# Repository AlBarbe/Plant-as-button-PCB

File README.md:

<!-- HEADER -->
# Plant as Button — PCB 🌱🔌

Wouldn't be cool to use as a plant a touch sensor? Now it has a proper board to live on.
This repo hosts the hardware side of the project — the companion firmware (the code that actually reads the plant's touch) lives in [Plant-as-button](https://github.com/AlBarbe/Plant-as-button).

<!-- TABLE OF CONTENTS -->
<!--
<details>
  <summary>Table of contenent</summary>
    <ul>
      <li></li><a href="#introduction">Introduction</a></li>
      <li></li><a href="#how-it-works">How it works</a></li>
      <li></li><a href="#repository-structure">Repository structure</a></li>
      <li></li><a href="#status--known-issues">Status & known issues</a></li>
    </ul>
</details>
-->
<!-- INTRODUCTION -->
## Introduction

This is my first PCB design, done in KiCad 9. The idea was to give the plant-as-button concept a real, standalone board instead of a breadboard: an ESP32-S3 module, its own power supply, and a driver stage so the "button" can actually control something (an RGBWW LED strip) when the plant is touched.

The board has been manufactured and it works. Every opinion or suggestion is more than welcome!!

<!-- PCB LAYOUT -->

<p align="center"><sub>PAB_V1 layout: power section (left), 5-channel LED driver (top), ESP32-S3-MINI-1 and full GPIO breakout (right)</sub></p>

<!-- HOW IT WORKS -->
## How it works
- ### Concept
  The board is built around an ESP32-S3-MINI-1 module, using the same capacitive touch trick described in the firmware repo: a touch-capable GPIO is wired to a pad, meant to be connected (by a simple cable) to the soil near the plant's roots. When a person touches the plant, the capacitance seen on that GPIO changes, and the microcontroller reads it as a "press".

- ### Power
  The board can be powered either from USB-C or from an external 12V supply (screw terminal), with a power mux (TPS2116) automatically selecting between the two. From there, two buck converters step the voltage down to 5V and then 3.3V for the MCU and the rest of the logic. The 12V input is protected with a TVS diode, and the USB data lines have their own ESD protection.

- ### LED driver
  Five low-side MOSFETs let the ESP32 switch a common-anode RGBWW LED strip (Red, Green, Blue, Warm White, Cool White), connected via a 6-pin screw terminal. The idea is the same as the firmware's trigger class: on touch, on release, or after a given time, drive one of the channels.

- ### Debug breakout
  Basically every GPIO of the module is broken out to its own test pad on the silkscreen (labeled with the pin function, not just a generic reference), on top of the usual RESET/BOOT buttons. This turned out to be very handy, see below.

## Repository structure
- `PAB_V1.kicad_pro / .kicad_sch / .kicad_pcb` — the KiCad 9 project (schematic + 4-layer PCB, single sheet).
- `Libraries/` — symbols, footprints and 3D models used by the project (kept local so the repo is self-contained).
- `Datasheets/` — datasheets of the main parts used.
- `BOM.ods` — bill of materials.
- `docs/images/` — renders/screenshots of the board (layout, etc.).

## Status & known issues
The board has been fabricated and is working. There is one known bug: the USB-UART bridge (CP2102) is not wired correctly to the ESP32-S3, so programming/monitoring through the on-board USB-C via the CP2102 doesn't work.
It's not a dead end though — the ESP32-S3 has its own native USB, and since every GPIO (including the native USB D+/D-) is broken out to a test pad, the board can still be flashed and debugged by using those pins directly, bypassing the CP2102 entirely.

## Implementation
Firmware-wise, this board is meant to be paired with the code from [Plant-as-button](https://github.com/AlBarbe/Plant-as-button): the touch pad on this PCB is where the plant's cable connects, and the LED terminal is a ready-made output for whatever trigger logic you build on top of it.

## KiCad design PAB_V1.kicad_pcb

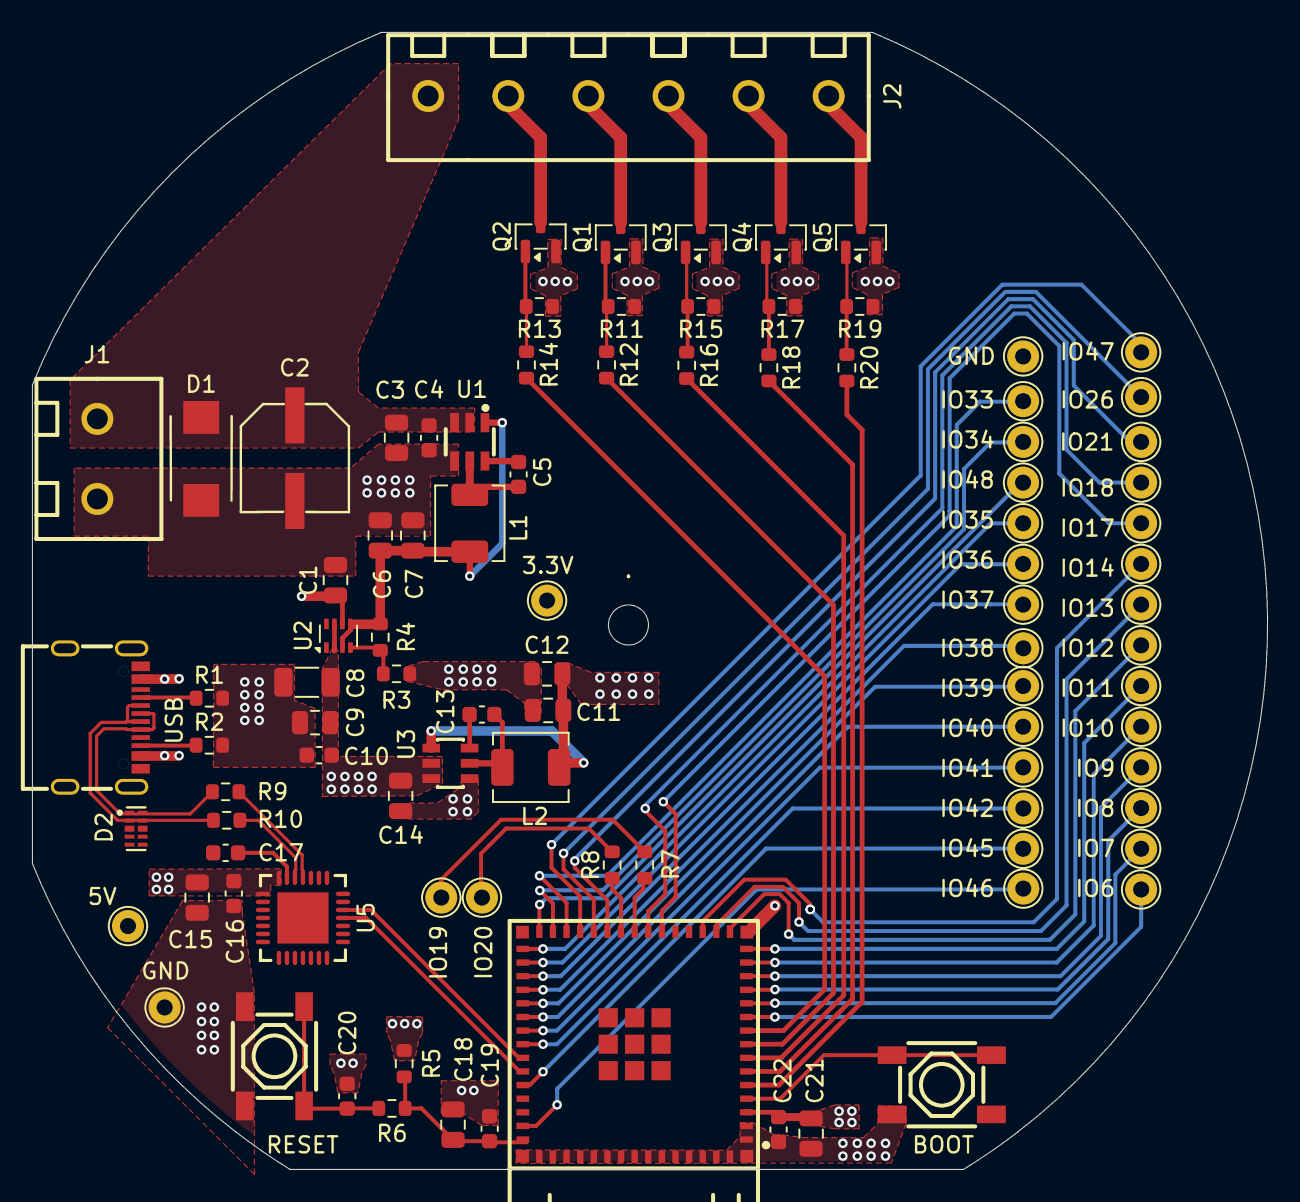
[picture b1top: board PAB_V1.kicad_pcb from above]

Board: 4 copper layers, 77.1 x 71.0 mm, 95 parts (0 on the bottom side), 67 nets.

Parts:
3.3V, 5V: Conn_01x01; TestPoint_THTPad_D2.0mm_Drill1.0mm
.: MountingHole_2.5mm
BOOT: BOOT; SW-SMD_4P-L5.2-W5.2-P3.70-LS6.5
C1, C3, C9, C14: 10μF; C_0805_2012Metric
C2: MA25V220M6X8; CAP-SMD_BD6.3-L6.6-W6.6-LS7.3-FD
C4, C5, C10, C13, C16, C17, C19, C20, C22: 100nF; C_0603_1608Metric
C6, C7, C11, C12, C21: 22μF; C_0805_2012Metric
C8: 47μF; C_1206_3216Metric
C15, C18: 1μF; C_0805_2012Metric
D1: SMBJ15CA; SMB_L4.6-W3.6-LS5.3-BI
D2: TPD4E05U06DQAR; USON-10_L2.5-W1.0-P0.50-BL
GND: Conn_01x01; TestPoint_THTPad_D2.0mm_Drill1.0mm
GND#2: Conn_01x01; TestPoint_THTPad_D2.0mm_Drill1.0mm
IO6, IO7, IO8, IO9, IO10, IO11, IO12, IO13, IO14, IO17, IO18, IO19, IO20, IO21, IO26, IO33, IO34, IO35, IO36, IO37, IO38, IO39, IO40, IO41, IO42, IO45, IO46, IO47, IO48: Conn_01x01; TestPoint_THTPad_D2.0mm_Drill1.0mm
J1: Screw_Terminal_01x02; CONN-TH_WJ126V-5.0-2P
J2: Screw_Terminal_01x06; CONN-TH_6P-P5.00_WJ126V-5.0-6P
L1, L2: 4.7μH; L_TechFuse_SL0420
Q1, Q2, Q3, Q4, Q5: AO3400A; SOT-23
R1, R2: 5.1KΩ; R_0603_1608Metric
R3, R4: 24KΩ; R_0603_1608Metric
R5: 10KΩ; R_0603_1608Metric
R6, R7, R8: 0Ω; R_0603_1608Metric
R9, R10, R12, R14, R16, R18, R20: 22Ω; R_0603_1608Metric
R11, R13, R15, R17, R19: 100KΩ; R_0603_1608Metric
RESET: RESET; SW-SMD_4P-L5.2-W5.2-P3.70-LS6.5
U1: AP63205WU-7; TSOT-23-6_L2.9-W1.6-P0.95-LS2.8-BL
U2: TPS2116DRL; SOT-583-8
U3: AP63203WU-7; TSOT-26_L2.9-W1.6-P0.95-LS2.8-BL
U4: ESP32-S3-MINI-1-N4R2; BULETM-SMD_ESP32-S3-MINI-1-N8
U5: CP2102-GMR; WQFN-28_L5.0-W5.0-P0.50-BL-EP3.2
USB: TYPE-C16PIN; USB-C-SMD_TYPE-C16PIN

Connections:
+3.3V: 3.3V.1, C11.1, C12.1, C21.2, C22.1, L2.2, R5.2, U3.1 (FB), U4.3 (3V3)
+5V: 5V.1, C8.2, C9.2, C10.2, C14.1, C15.1, C16.1, U2.2 (VOUT), U2.7 (VOUT), U3.2 (EN), U3.3 (VIN), U5.7 (REGIN), U5.8 (VBUS)
+5V_PS: C6.1, C7.1, L1.1, R4.2, U1.1 (FB), U2.3 (VIN1), U2.5 (MODE)
+5V_USB: C1.1, D2.4 (D2+), D2.7 (NC), U2.6 (VIN2), USB.A4B9 (VBUS), USB.B4A9 (VBUS)
+12V: C2.1, C3.2, C4.2, D1.2 (A), J1.1, J2.6, U1.2 (EN), U1.3 (VIN)
/BOOT: BOOT.3, BOOT.4, U4.4 (IO0)
/EN: C18.2, C19.1, R5.1, R6.2, U4.45 (EN)
Blue: J2.3, Q3.3 (D)
C_White: J2.1, Q5.3 (D)
GND: BOOT.2, C1.2, C2.2, C3.1, C4.1, C6.2, C7.2, C8.1, C9.1, C10.1, C11.2, C12.2, C14.2, C15.2, C16.2, C17.1, C18.1, C19.2, C20.2, C21.1, C22.2, D1.1 (K), D2.3 (GND), D2.8 (GND), GND.1, GND#2.1, J1.2, Q1.2 (S), Q2.2 (S), Q3.2 (S), Q4.2 (S), Q5.2 (S), R1.2, R2.2, R3.1, R11.1, R13.1, R15.1, R17.1, R19.1, RESET.1, RESET.2, U1.4 (GND), U2.1 (GND), U3.4 (GND), U4.1 (GND), U4.2 (GND), U4.42 (GND), U4.43 (GND), U4.46 (GND), U4.47 (GND), U4.48 (GND), U4.49 (GND), U4.50 (GND), U4.51 (GND), U4.52 (GND), U4.53 (GND), U4.54 (GND), U4.55 (GND), U4.56 (GND), U4.57 (GND), U4.58 (GND), U4.59 (GND), U4.60 (GND), U4.GND, U5.3 (GND), USB.1 (SHELL), USB.2 (SHELL), USB.3 (SHELL), USB.4 (SHELL), USB.A1B12 (GND), USB.B1A12 (GND)
GPIO1: R20.2, U4.5 (IO1)
GPIO2: R18.2, U4.6 (IO2)
GPIO3: R16.2, U4.7 (IO3)
GPIO4: R12.2, U4.8 (IO4)
GPIO5: R14.2, U4.9 (IO5)
GPIO6: IO6.1, U4.10 (IO6)
GPIO7: IO7.1, U4.11 (IO7)
GPIO8: IO8.1, U4.12 (IO8)
GPIO9: IO9.1, U4.13 (IO9)
GPIO10: IO10.1, U4.14 (IO10)
GPIO11: IO11.1, U4.15 (IO11)
GPIO12: IO12.1, U4.16 (IO12)
GPIO13: IO13.1, U4.17 (IO13)
GPIO14: IO14.1, U4.18 (IO14)
GPIO17: IO17.1, U4.21 (IO17)
GPIO18: IO18.1, U4.22 (IO18)
GPIO19: IO19.1, R7.2
GPIO20: IO20.1, R8.1
GPIO21: IO21.1, U4.25 (IO21)
GPIO26: IO26.1, U4.26 (IO26)
GPIO33: IO33.1, U4.28 (IO33)
GPIO34: IO34.1, U4.29 (IO34)
GPIO35: IO35.1, U4.31 (IO35)
GPIO36: IO36.1, U4.32 (IO36)
GPIO37: IO37.1, U4.33 (IO37)
GPIO38: IO38.1, U4.34 (IO38)
GPIO39: IO39.1, U4.35 (IO39)
GPIO40: IO40.1, U4.36 (IO40)
GPIO41: IO41.1, U4.37 (IO41)
GPIO42: IO42.1, U4.38 (IO42)
GPIO45: IO45.1, U4.41 (IO45)
GPIO46: IO46.1, U4.44 (IO46)
GPIO47: IO47.1, U4.27 (IO47)
GPIO48: IO48.1, U4.30 (IO48)
Green: J2.5, Q2.3 (D)
unnamed: C20.1, R6.1, RESET.3, RESET.4
unnamed: Q1.1 (G), R11.2, R12.1
unnamed: Q2.1 (G), R13.2, R14.1
unnamed: Q3.1 (G), R15.2, R16.1
unnamed: Q4.1 (G), R17.2, R18.1
unnamed: Q5.1 (G), R19.2, R20.1
unnamed: C5.1, U1.6 (BST)
unnamed: C5.2, L1.2, U1.5 (SW)
unnamed: R3.2, R4.1, U2.4 (PR1)
unnamed: C13.2, U3.6 (BST)
unnamed: C13.1, L2.1, U3.5 (SW)
unnamed: R7.1, U4.23 (IO19)
unnamed: R8.2, U4.24 (IO20)
unnamed: C17.2, U5.6 (VDD)
unnamed: R1.1, USB.A5 (CC1)
unnamed: R2.1, USB.B5 (CC2)
RXD0: U4.40 (RXD0), U5.25 (RXD)
Red: J2.4, Q1.3 (D)
TXD0: U4.39 (TXD0), U5.26 (TXD)
USB_DN: D2.2 (D1-), D2.9 (NC), R10.1, R10.2, U5.5 (D-), USB.A7 (DN1), USB.B7 (DN2)
USB_DP: D2.1 (D1+), D2.10 (NC), R9.1, R9.2, U5.4 (D+), USB.A6 (DP1), USB.B6 (DP2)
W_White: J2.2, Q4.3 (D)

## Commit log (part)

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2025-09-13 Project start: created power supply
2025-09-13 First upload: Creation of the project, created power supply related circuit
2025-09-16 Added ESP32-S3FN8, and made some circuitry
2025-09-24 Choose esp32-s3-mini1 instead, and AP63203 as 5V to 3.3V instead ldo converter
2025-09-27 added esp32 and uart circuitry, cleaned chart
2025-09-27 Compleated first design, mst be checked and added properly connector
2025-09-30 Added TVS to 12V input, reorganized names, reorganized structures
2025-10-03 Changed whole symbol and footprint library, used easyeda2kicad converted from jlc part.
2025-10-03 Added most of the component footprint need specs for capacitor types and dimension
2025-10-19 Macbook project test upload
2025-10-19 Added Bulk capacitor, corrected stuff, checked things
2025-10-19 Added schematic PDF
2025-10-21 Correction to basic component value
2025-10-21 added decoupling capacitors, added capacitor footprint
2025-10-22 small update
2025-10-22 error test resolving
2025-10-24 filled part/footprint file (proto bom file)
2025-10-25 resolving error, added bom file
2025-11-02 organized netclasses
2025-11-04 starting placing component
2025-11-06 going on with PCB design
2025-11-07 going on with pcb layout
2025-12-15 added vias, updated project
2026-01-01 going on with connections
2026-01-10 3D file path correction
2026-01-10 reorganized text layout
